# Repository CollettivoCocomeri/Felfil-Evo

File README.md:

# Felfil Evo
Evolved open source DIY 3D printer filament extruder

In this folder you will find all you need to replicate, modify and implement Felfil Evo

Contents of the folder:

- 3D-Model
- BOM
- Electronics
- FEBK - Basic Kit
- License

Last update: 18/07/2016

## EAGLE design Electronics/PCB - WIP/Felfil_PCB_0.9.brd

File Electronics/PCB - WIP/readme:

This is the WIP of the brand new PCB of Felfil Evo.

It's not ready, now is going to be tested.

---
PCB Release Date: 09/06/2016
PCB Version: 0.9
---

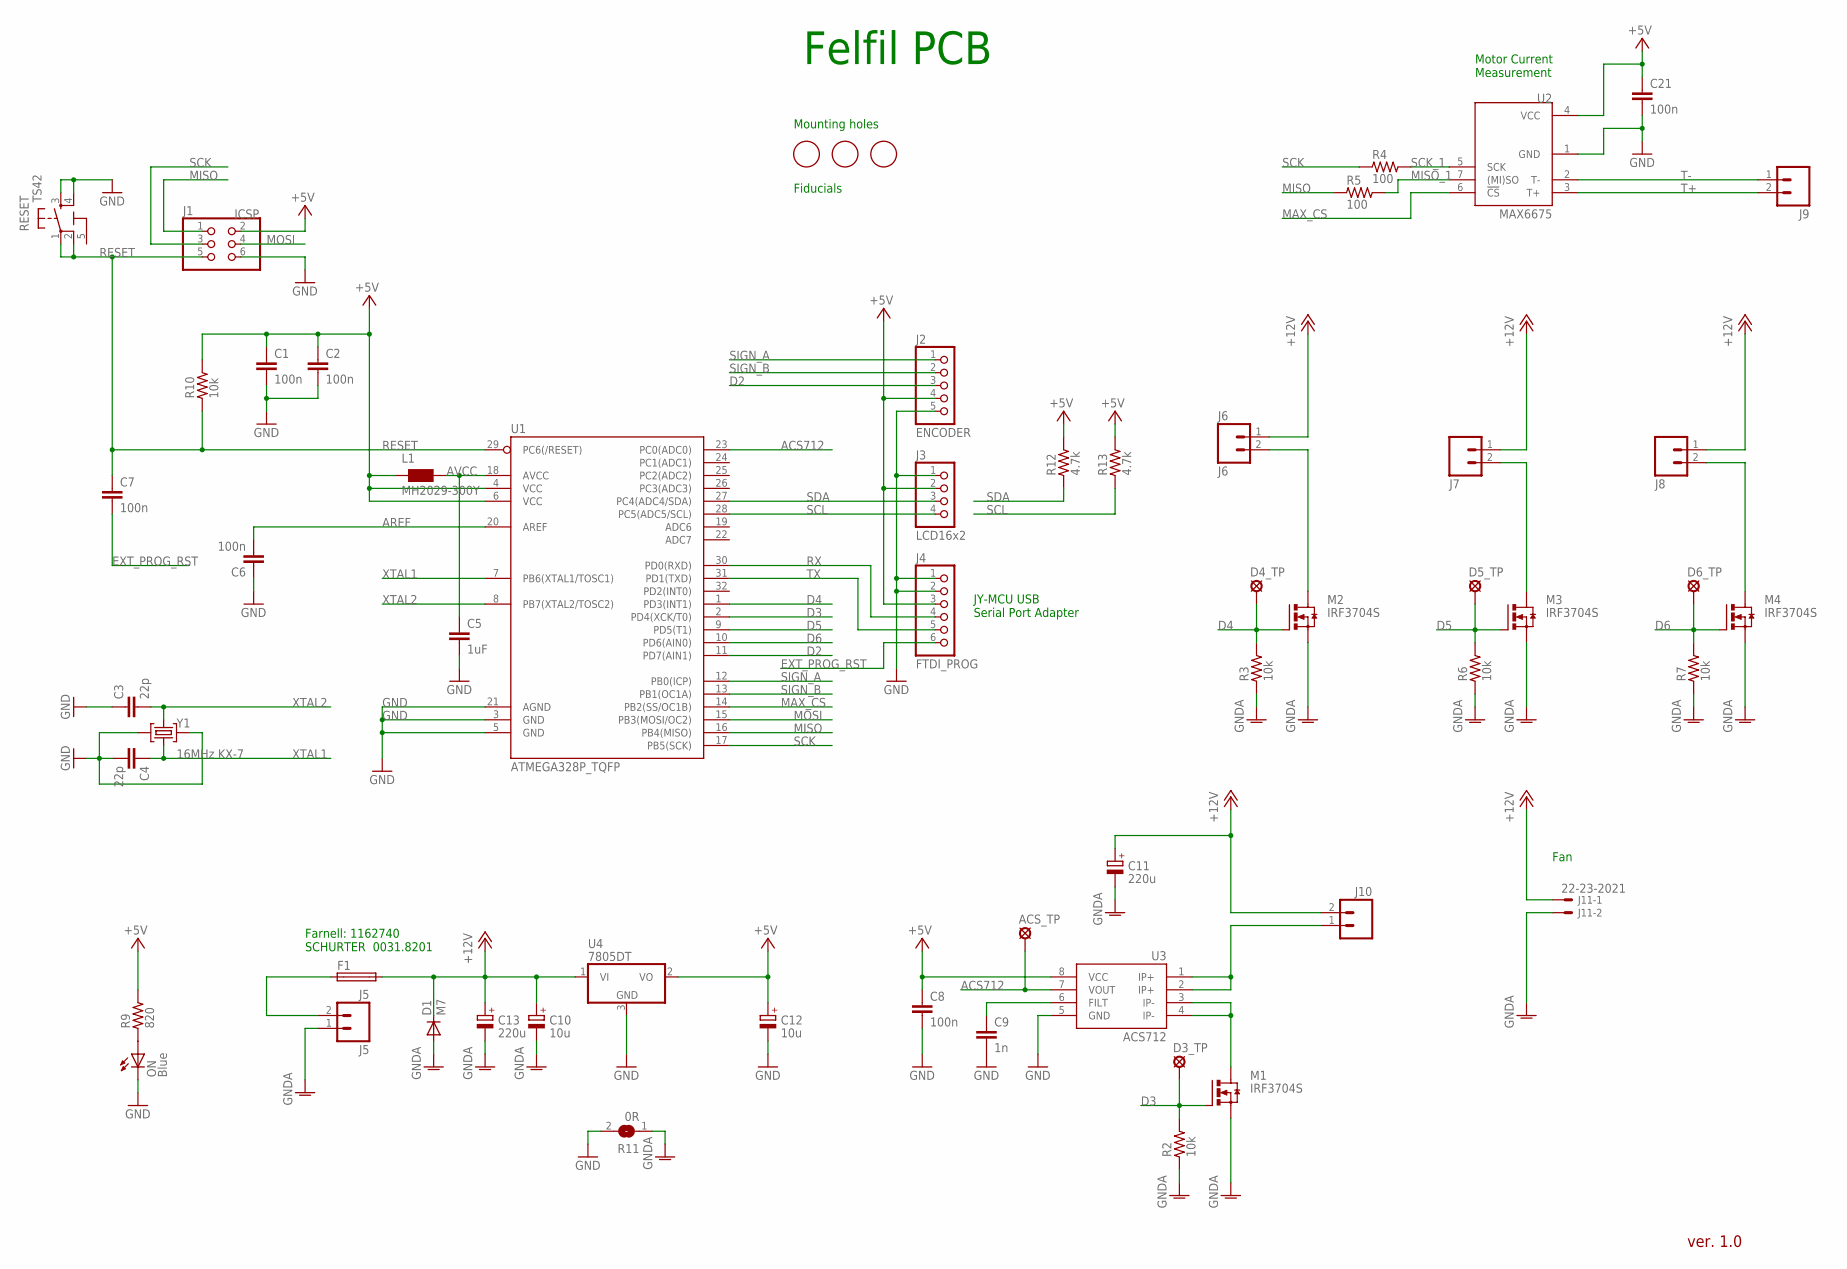
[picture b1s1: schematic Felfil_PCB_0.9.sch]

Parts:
ACS_TP: LSP11
C1, C2, C6, C7, C8, C21: 100n; C0603K
C3, C4: 22p; C0603K
C5: 1uF; C0603K
C9: 1n; C0603K
C10, C12: 10u; SMC_B
C11, C13: 220u; PANASONIC_F
D1: M7; SMB
D3_TP, D4_TP, D5_TP, D6_TP: LSP11
F1: FUSEBLANK_5X20MM; FUSE_HOLDER_5X20MM
FID1, FID2, FID3: FIDUCIALMOUNT; FIDUCIA-MOUNT
J1: ICSP; 2X03
J2: ENCODER; 1X05
J3: LCD16x2; 1X04
J4: FTDI_PROG; 1X06
J5: J5; SCREWTERMINAL-5MM-2
J6: J6; SCREWTERMINAL-5MM-2
J7, J8, J9, J10: M025MM; SCREWTERMINAL-5MM-2
J11: 22-23-2021
L1: MH2029-300Y; 0805
M1, M2, M3, M4: IRF3704S; D2PACK
ON: Blue; CHIPLED_0805
R2, R3, R6, R7, R10: 10k; R0603
R4, R5: 100; R0603
R9: 820; R0603
R11: 0R; SJW
R12, R13: 4.7k; R0603
RESET: TS42
U1: ATMEGA328P_TQFP; TQFP32-08
U2: MAX6675; SOIC8
U3: ACS712; SO08
U4: 7805DT; TO252
Y1: 16MHz KX-7; CRYSTAL-3.2-2.5

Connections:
5-GND: RESET.5 (5-GND)
+5V: C1.1, C2.1, C8.1, C12.+, C21.1, J1.2, J2.4, J3.2, J4.3, L1.1, R9.2, R10.2, R12.2, R13.2, U1.4 (VCC), U1.6 (VCC), U2.4 (VCC), U3.8 (VCC), U4.2 (VO)
+12V: C10.+, C11.+, C13.+, D1.C, F1.2, J6.1, J7.1, J8.1, J10.2, J11.1, U4.1 (VI)
ACS712: ACS_TP.MP, U1.23 (PC0(ADC0)), U3.7 (VOUT)
AREF: C6.2, U1.20 (AREF)
AVCC: C5.1, L1.2, U1.18 (AVCC)
D2: J2.3, U1.11 (PD7(AIN1))
D3: D3_TP.MP, M1.1 (G), R2.2, U1.2 (PD4(XCK/T0))
D4: D4_TP.MP, M2.1 (G), R3.2, U1.1 (PD3(INT1))
D5: D5_TP.MP, M3.1 (G), R6.2, U1.9 (PD5(T1))
D6: D6_TP.MP, M4.1 (G), R7.2, U1.10 (PD6(AIN0))
EXT_PROG_RST: C7.2, J4.6
GND: C1.2, C2.2, C3.1, C4.2, C5.2, C6.1, C8.2, C9.2, C12.-, C21.2, J1.6, J2.5, J3.1, J4.1, J4.2, ON.C, R11.2, RESET.3, RESET.4, U1.3 (GND), U1.5 (GND), U1.21 (AGND), U2.1 (GND), U3.5 (GND), U4.3 (GND), Y1.2 (GND), Y1.4 (GND)
GNDA: C10.-, C11.-, C13.-, D1.A, J5.1, J11.2, M1.3 (S), M2.3 (S), M3.3 (S), M4.3 (S), R2.1, R3.1, R6.1, R7.1, R11.1
MAX_CS: U1.14 (PB2(SS/OC1B)), U2.6 (!CS)
MISO: J1.1, R5.1, U1.16 (PB4(MISO))
MISO_1: R5.2, U2.7 ((MI)SO)
MOSI: J1.4, U1.15 (PB3(MOSI/OC2))
unnamed: C9.1, U3.6 (FILT)
unnamed: M1.2 (D), U3.3 (IP-), U3.4 (IP-)
unnamed: F1.1, J5.2
unnamed: ON.A, R9.1
unnamed: J10.1, U3.1 (IP+), U3.2 (IP+)
unnamed: J6.2, M2.2 (D)
unnamed: J7.2, M3.2 (D)
unnamed: J8.2, M4.2 (D)
RESET: C7.1, J1.5, R10.1, RESET.1, RESET.2, U1.29 (PC6(/RESET))
RX: J4.4, U1.30 (PD0(RXD))
SCK: J1.3, R4.1, U1.17 (PB5(SCK))
SCK_1: R4.2, U2.5 (SCK)
SCL: J3.4, R13.1, U1.28 (PC5(ADC5/SCL))
SDA: J3.3, R12.1, U1.27 (PC4(ADC4/SDA))
SIGN_A: J2.1, U1.12 (PB0(ICP))
SIGN_B: J2.2, U1.13 (PB1(OC1A))
T+: J9.2, U2.3 (T+)
T-: J9.1, U2.2 (T-)
TX: J4.5, U1.31 (PD1(TXD))
XTAL1: C4.1, U1.7 (PB6(XTAL1/TOSC1)), Y1.1 (C1)
XTAL2: C3.2, U1.8 (PB7(XTAL2/TOSC2)), Y1.3 (C2)

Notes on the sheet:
Felfil PCB
JY-MCU USB Serial Port Adapter
Mounting holes
Motor Current Measurement
Farnell: 1162740 SCHURTER 0031.8201
ver. 1.0
Fiducials
Fan

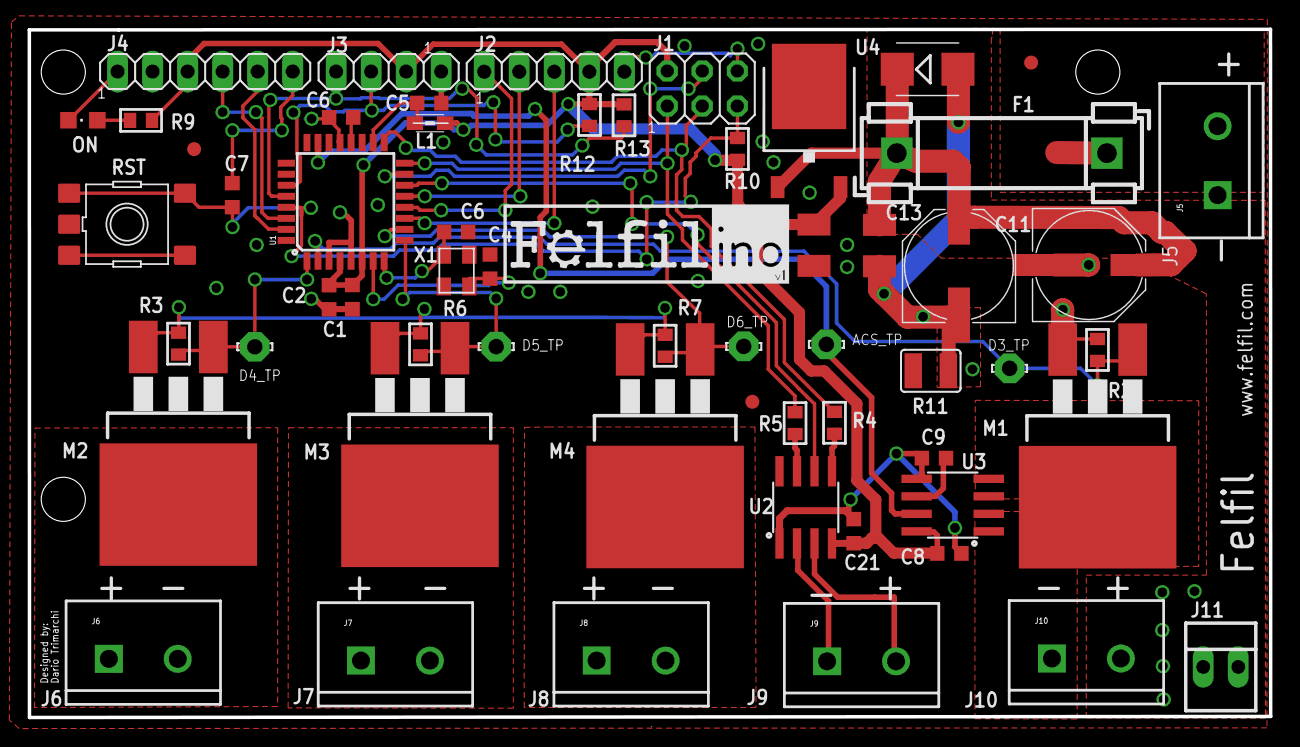
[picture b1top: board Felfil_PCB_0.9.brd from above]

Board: 2 copper layers, 90.0 x 49.9 mm, 58 parts (0 on the bottom side), 38 nets.

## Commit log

2015-10-26 Create bom
2015-10-26 Techs
    Techs
2015-10-26 Update bom
2015-10-26 Electronics
    Electronics
2015-10-26 Create License
2015-11-16 libraries
2015-11-17 Create BOM for makers with Felfil Evo Basic Kit
2015-11-17 Rename bom to BOM
2015-11-20 Update BOM for makers with Felfil Evo Basic Kit
2016-03-23 Modulo temperatura + Conversione progetto a Visual Studio
2016-06-09 update 09/06/2016
2016-06-20 Added 3d model for Basic Kit
2016-06-20 Lighter 3d model
2016-07-18 Added FEBK
2016-10-20 name changed
2016-12-01 Revert "Modulo temperatura + Conversione progetto a Visual Studio"
    This reverts commit 7d116971531fbad943f1c42d7904d019b56a0802.
2016-12-01 Felfil 0.9
    felfil-evo beta version
2017-01-04 Sketch update
2017-01-18 update menu + lcd
    -attesa iniziale raggiungimento temperatura
    -settaggio iniziale pwm
    -modifica visualizzazione pwm
    -feedback heating
2017-01-18 riorganizzazione directory
2017-03-28 Update 28032017
    Firmware V.0.9 - Felfil Evo Model1.2 - Printable hopper
2017-03-29 Translate-marks
2017-05-04 HowToUpdateFelfilEvoFirmware + Firmware ver 0.9.1
    Update guide, bug fix
2017-11-08 Lib_UP_Fix
2018-05-11 Updt
2020-03-09 GearMotor
2021-09-22 Add files via upload
    o Seperation of functions definition from FelfilMenu.h
    o Little refactoring
    o Add of management for hardware malfunction
    "SENSOR_ERROR" // max6675 rotto -> temp = 750, termocoppia al contrario -> temp = 0
    "TERMAL_PROBE" // temperatura non sale quando scalda
    "PROBE_CONTACT" // c'è un intervallo troppo elevato tra un valore letto e il precedenze
2021-10-07 Add files via upload
    High temperatures heating bug correction
2021-10-13 Add files via upload
    Change name errors

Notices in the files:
parts and their libraries:
rc-master: Copyright (C) 2007, Bob Starr
SparkFun-DigitalIC: Licensing: Creative Commons ShareAlike 4.0 International - https://creativecommons.org/licenses/by-sa/4.0
